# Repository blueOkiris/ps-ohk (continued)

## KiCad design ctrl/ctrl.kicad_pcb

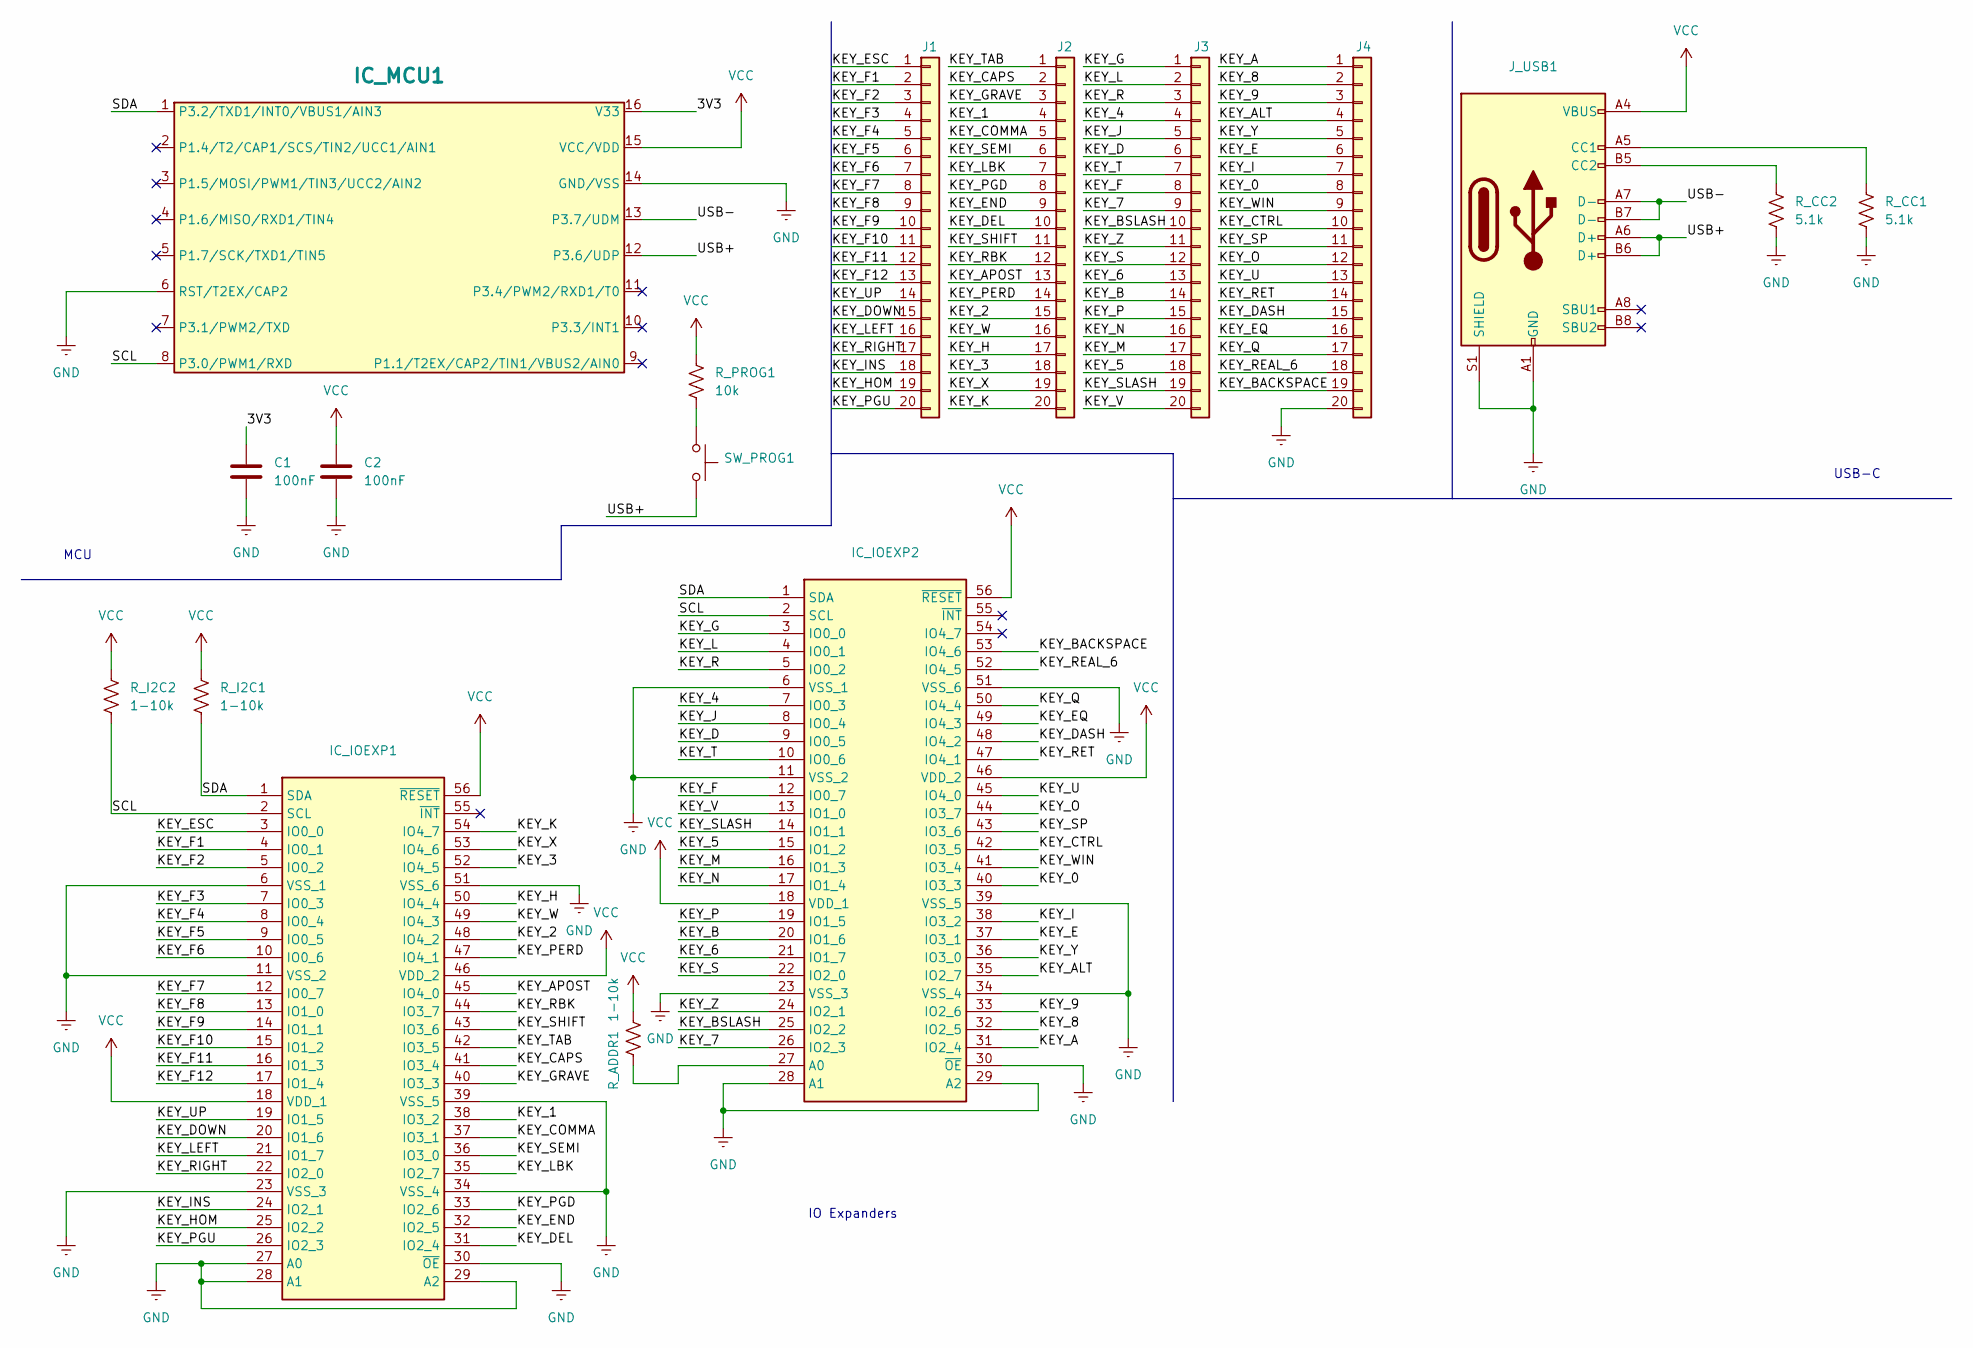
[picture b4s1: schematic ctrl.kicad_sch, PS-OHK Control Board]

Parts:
C1, C2: 100nF; C_0603_1608Metric
IC_IOEXP1, IC_IOEXP2: SOP50P810X120-56N; Mouser Part Number 771-PCA9505DGGY
IC_MCU1: SOIC-16_3.9x9.9mm_Pitch1.27mm
J1, J2, J3, J4: Conn_01x20; PinHeader_1x20_P2.54mm_Vertical
J_USB1: USB_C_Receptacle_HCTL_HC-TYPE-C-16P-01A
R_ADDR1: 1-10k; R_0603_1608Metric
R_CC1, R_CC2: 5.1k; R_0603_1608Metric
R_I2C1, R_I2C2: 1-10k; R_0603_1608Metric
R_PROG1: 10k; R_0603_1608Metric
SW_PROG1: SW_Push_1P1T_NO_6x6mm_H9.5mm

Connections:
/3V3: C1.1, IC_MCU1.16 (V33)
/KEY_0: IC_IOEXP2.40 (IO3_3), J4.8
/KEY_1: IC_IOEXP1.38 (IO3_2), J2.4
/KEY_2: IC_IOEXP1.48 (IO4_2), J2.15
/KEY_3: IC_IOEXP1.52 (IO4_5), J2.18
/KEY_4: IC_IOEXP2.7 (IO0_3), J3.4
/KEY_5: IC_IOEXP2.15 (IO1_2), J3.18
/KEY_6: IC_IOEXP2.21 (IO1_7), J3.13
/KEY_7: IC_IOEXP2.26 (IO2_3), J3.9
/KEY_8: IC_IOEXP2.32 (IO2_5), J4.2
/KEY_9: IC_IOEXP2.33 (IO2_6), J4.3
/KEY_A: IC_IOEXP2.31 (IO2_4), J4.1
/KEY_ALT: IC_IOEXP2.35 (IO2_7), J4.4
/KEY_APOST: IC_IOEXP1.45 (IO4_0), J2.13
/KEY_B: IC_IOEXP2.20 (IO1_6), J3.14
/KEY_BACKSPACE: IC_IOEXP2.53 (IO4_6), J4.19
/KEY_BSLASH: IC_IOEXP2.25 (IO2_2), J3.10
/KEY_CAPS: IC_IOEXP1.41 (IO3_4), J2.2
/KEY_COMMA: IC_IOEXP1.37 (IO3_1), J2.5
/KEY_CTRL: IC_IOEXP2.42 (IO3_5), J4.10
/KEY_D: IC_IOEXP2.9 (IO0_5), J3.6
/KEY_DASH: IC_IOEXP2.48 (IO4_2), J4.15
/KEY_DEL: IC_IOEXP1.31 (IO2_4), J2.10
/KEY_DOWN: IC_IOEXP1.20 (IO1_6), J1.15
/KEY_E: IC_IOEXP2.37 (IO3_1), J4.6
/KEY_END: IC_IOEXP1.32 (IO2_5), J2.9
/KEY_EQ: IC_IOEXP2.49 (IO4_3), J4.16
/KEY_ESC: IC_IOEXP1.3 (IO0_0), J1.1
/KEY_F: IC_IOEXP2.12 (IO0_7), J3.8
/KEY_F1: IC_IOEXP1.4 (IO0_1), J1.2
/KEY_F2: IC_IOEXP1.5 (IO0_2), J1.3
/KEY_F3: IC_IOEXP1.7 (IO0_3), J1.4
/KEY_F4: IC_IOEXP1.8 (IO0_4), J1.5
/KEY_F5: IC_IOEXP1.9 (IO0_5), J1.6
/KEY_F6: IC_IOEXP1.10 (IO0_6), J1.7
/KEY_F7: IC_IOEXP1.12 (IO0_7), J1.8
/KEY_F8: IC_IOEXP1.13 (IO1_0), J1.9
/KEY_F9: IC_IOEXP1.14 (IO1_1), J1.10
/KEY_F10: IC_IOEXP1.15 (IO1_2), J1.11
/KEY_F11: IC_IOEXP1.16 (IO1_3), J1.12
/KEY_F12: IC_IOEXP1.17 (IO1_4), J1.13
/KEY_G: IC_IOEXP2.3 (IO0_0), J3.1
/KEY_GRAVE: IC_IOEXP1.40 (IO3_3), J2.3
/KEY_H: IC_IOEXP1.50 (IO4_4), J2.17
/KEY_HOM: IC_IOEXP1.25 (IO2_2), J1.19
/KEY_I: IC_IOEXP2.38 (IO3_2), J4.7
/KEY_INS: IC_IOEXP1.24 (IO2_1), J1.18
/KEY_J: IC_IOEXP2.8 (IO0_4), J3.5
/KEY_K: IC_IOEXP1.54 (IO4_7), J2.20
/KEY_L: IC_IOEXP2.4 (IO0_1), J3.2
/KEY_LBK: IC_IOEXP1.35 (IO2_7), J2.7
/KEY_LEFT: IC_IOEXP1.21 (IO1_7), J1.16
/KEY_M: IC_IOEXP2.16 (IO1_3), J3.17
/KEY_N: IC_IOEXP2.17 (IO1_4), J3.16
/KEY_O: IC_IOEXP2.44 (IO3_7), J4.12
/KEY_P: IC_IOEXP2.19 (IO1_5), J3.15
/KEY_PERD: IC_IOEXP1.47 (IO4_1), J2.14
/KEY_PGD: IC_IOEXP1.33 (IO2_6), J2.8
/KEY_PGU: IC_IOEXP1.26 (IO2_3), J1.20
/KEY_Q: IC_IOEXP2.50 (IO4_4), J4.17
/KEY_R: IC_IOEXP2.5 (IO0_2), J3.3
/KEY_RBK: IC_IOEXP1.44 (IO3_7), J2.12
/KEY_REAL_6: IC_IOEXP2.52 (IO4_5), J4.18
/KEY_RET: IC_IOEXP2.47 (IO4_1), J4.14
/KEY_RIGHT: IC_IOEXP1.22 (IO2_0), J1.17
/KEY_S: IC_IOEXP2.22 (IO2_0), J3.12
/KEY_SEMI: IC_IOEXP1.36 (IO3_0), J2.6
/KEY_SHIFT: IC_IOEXP1.43 (IO3_6), J2.11
/KEY_SLASH: IC_IOEXP2.14 (IO1_1), J3.19
/KEY_SP: IC_IOEXP2.43 (IO3_6), J4.11
/KEY_T: IC_IOEXP2.10 (IO0_6), J3.7
/KEY_TAB: IC_IOEXP1.42 (IO3_5), J2.1
/KEY_U: IC_IOEXP2.45 (IO4_0), J4.13
/KEY_UP: IC_IOEXP1.19 (IO1_5), J1.14
/KEY_V: IC_IOEXP2.13 (IO1_0), J3.20
/KEY_W: IC_IOEXP1.49 (IO4_3), J2.16
/KEY_WIN: IC_IOEXP2.41 (IO3_4), J4.9
/KEY_X: IC_IOEXP1.53 (IO4_6), J2.19
/KEY_Y: IC_IOEXP2.36 (IO3_0), J4.5
/KEY_Z: IC_IOEXP2.24 (IO2_1), J3.11
/SCL: IC_IOEXP1.2 (SCL), IC_IOEXP2.2 (SCL), IC_MCU1.8 (P3.0/PWM1/RXD), R_I2C2.2
/SDA: IC_IOEXP1.1 (SDA), IC_IOEXP2.1 (SDA), IC_MCU1.1 (P3.2/TXD1/INT0/VBUS1/AIN3), R_I2C1.2
/USB+: IC_MCU1.12 (P3.6/UDP), J_USB1.A6 (D+), J_USB1.B6 (D+), SW_PROG1.2
/USB-: IC_MCU1.13 (P3.7/UDM), J_USB1.A7 (D-), J_USB1.B7 (D-)
GND: C1.2, C2.2, IC_IOEXP1.6 (VSS_1), IC_IOEXP1.11 (VSS_2), IC_IOEXP1.23 (VSS_3), IC_IOEXP1.27 (A0), IC_IOEXP1.28 (A1), IC_IOEXP1.29 (A2), IC_IOEXP1.30 (~OE), IC_IOEXP1.34 (VSS_4), IC_IOEXP1.39 (VSS_5), IC_IOEXP1.51 (VSS_6), IC_IOEXP2.6 (VSS_1), IC_IOEXP2.11 (VSS_2), IC_IOEXP2.23 (VSS_3), IC_IOEXP2.28 (A1), IC_IOEXP2.29 (A2), IC_IOEXP2.30 (~OE), IC_IOEXP2.34 (VSS_4), IC_IOEXP2.39 (VSS_5), IC_IOEXP2.51 (VSS_6), IC_MCU1.6 (RST/T2EX/CAP2), IC_MCU1.14 (GND/VSS), J4.20, J_USB1.A1 (GND), J_USB1.A12 (GND), J_USB1.B1 (GND), J_USB1.B12 (GND), J_USB1.S1 (SHIELD), R_CC1.2, R_CC2.2
unnamed: IC_IOEXP2.27 (A0), R_ADDR1.2
unnamed: J_USB1.A5 (CC1), R_CC1.1
unnamed: J_USB1.B5 (CC2), R_CC2.1
unnamed: R_PROG1.2, SW_PROG1.1
VCC: C2.1, IC_IOEXP1.18 (VDD_1), IC_IOEXP1.46 (VDD_2), IC_IOEXP1.56 (~RESET), IC_IOEXP2.18 (VDD_1), IC_IOEXP2.46 (VDD_2), IC_IOEXP2.56 (~RESET), IC_MCU1.15 (VCC/VDD), J_USB1.A4 (VBUS), J_USB1.A9 (VBUS), J_USB1.B4 (VBUS), J_USB1.B9 (VBUS), R_ADDR1.1, R_I2C1.1, R_I2C2.1, R_PROG1.1

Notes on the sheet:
IO Expanders
USB-C
MCU

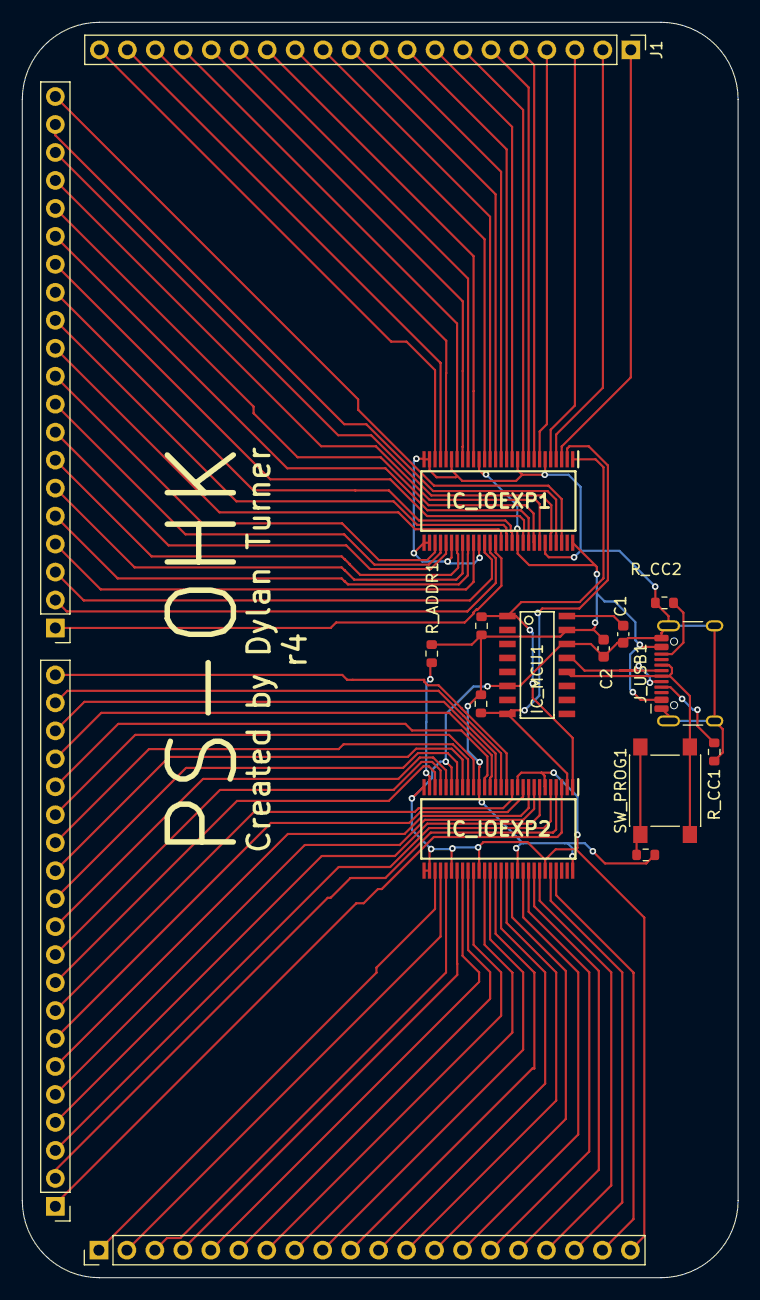
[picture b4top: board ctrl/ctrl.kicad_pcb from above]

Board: 2 copper layers, 65.0 x 114.0 mm, 17 parts (0 on the bottom side), 90 nets.

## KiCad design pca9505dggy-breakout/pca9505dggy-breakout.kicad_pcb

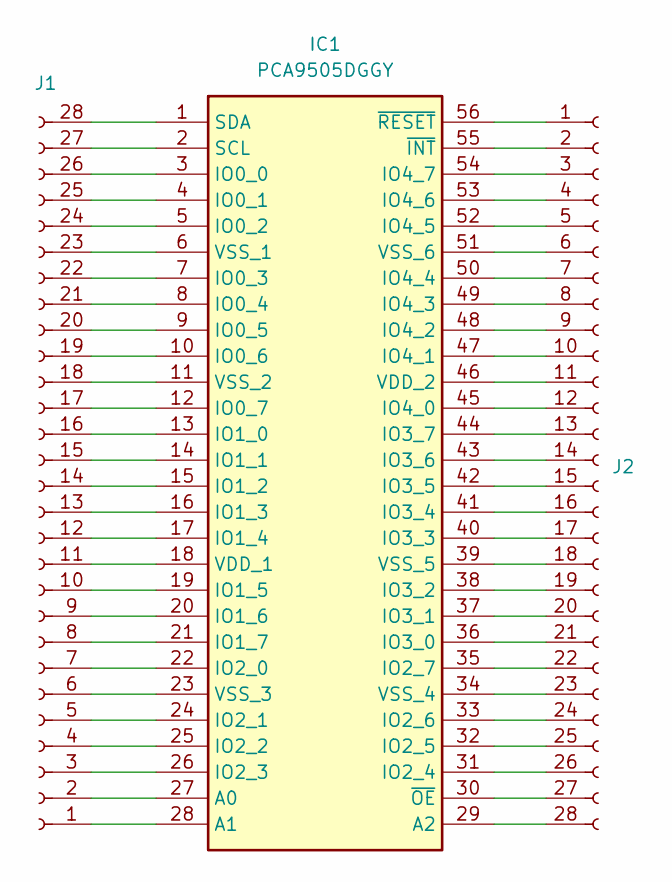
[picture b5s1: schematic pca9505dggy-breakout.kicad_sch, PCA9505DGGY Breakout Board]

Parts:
IC1: PCA9505DGGY; SOP50P810X120-56N; Mouser Part Number 771-PCA9505DGGY
J1, J2: PinHeader_1x28_P2.54mm_Vertical

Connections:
unnamed: IC1.27 (A0), J1.2
unnamed: IC1.28 (A1), J1.1
unnamed: IC1.29 (A2), J2.28
unnamed: IC1.3 (IO0_0), J1.26
unnamed: IC1.4 (IO0_1), J1.25
unnamed: IC1.5 (IO0_2), J1.24
unnamed: IC1.7 (IO0_3), J1.22
unnamed: IC1.8 (IO0_4), J1.21
unnamed: IC1.9 (IO0_5), J1.20
unnamed: IC1.10 (IO0_6), J1.19
unnamed: IC1.12 (IO0_7), J1.17
unnamed: IC1.13 (IO1_0), J1.16
unnamed: IC1.14 (IO1_1), J1.15
unnamed: IC1.15 (IO1_2), J1.14
unnamed: IC1.16 (IO1_3), J1.13
unnamed: IC1.17 (IO1_4), J1.12
unnamed: IC1.19 (IO1_5), J1.10
unnamed: IC1.20 (IO1_6), J1.9
unnamed: IC1.21 (IO1_7), J1.8
unnamed: IC1.22 (IO2_0), J1.7
unnamed: IC1.24 (IO2_1), J1.5
unnamed: IC1.25 (IO2_2), J1.4
unnamed: IC1.26 (IO2_3), J1.3
unnamed: IC1.31 (IO2_4), J2.26
unnamed: IC1.32 (IO2_5), J2.25
unnamed: IC1.33 (IO2_6), J2.24
unnamed: IC1.35 (IO2_7), J2.22
unnamed: IC1.36 (IO3_0), J2.21
unnamed: IC1.37 (IO3_1), J2.20
unnamed: IC1.38 (IO3_2), J2.19
unnamed: IC1.40 (IO3_3), J2.17
unnamed: IC1.41 (IO3_4), J2.16
unnamed: IC1.42 (IO3_5), J2.15
unnamed: IC1.43 (IO3_6), J2.14
unnamed: IC1.44 (IO3_7), J2.13
unnamed: IC1.45 (IO4_0), J2.12
unnamed: IC1.47 (IO4_1), J2.10
unnamed: IC1.48 (IO4_2), J2.9
unnamed: IC1.49 (IO4_3), J2.8
unnamed: IC1.50 (IO4_4), J2.7
unnamed: IC1.52 (IO4_5), J2.5
unnamed: IC1.53 (IO4_6), J2.4
unnamed: IC1.54 (IO4_7), J2.3
unnamed: IC1.2 (SCL), J1.27
unnamed: IC1.1 (SDA), J1.28
unnamed: IC1.18 (VDD_1), J1.11
unnamed: IC1.46 (VDD_2), J2.11
unnamed: IC1.6 (VSS_1), J1.23
unnamed: IC1.11 (VSS_2), J1.18
unnamed: IC1.23 (VSS_3), J1.6
unnamed: IC1.34 (VSS_4), J2.23
unnamed: IC1.39 (VSS_5), J2.18
unnamed: IC1.51 (VSS_6), J2.6
unnamed: IC1.55 (~INT), J2.2
unnamed: IC1.30 (~OE), J2.27
unnamed: IC1.56 (~RESET), J2.1

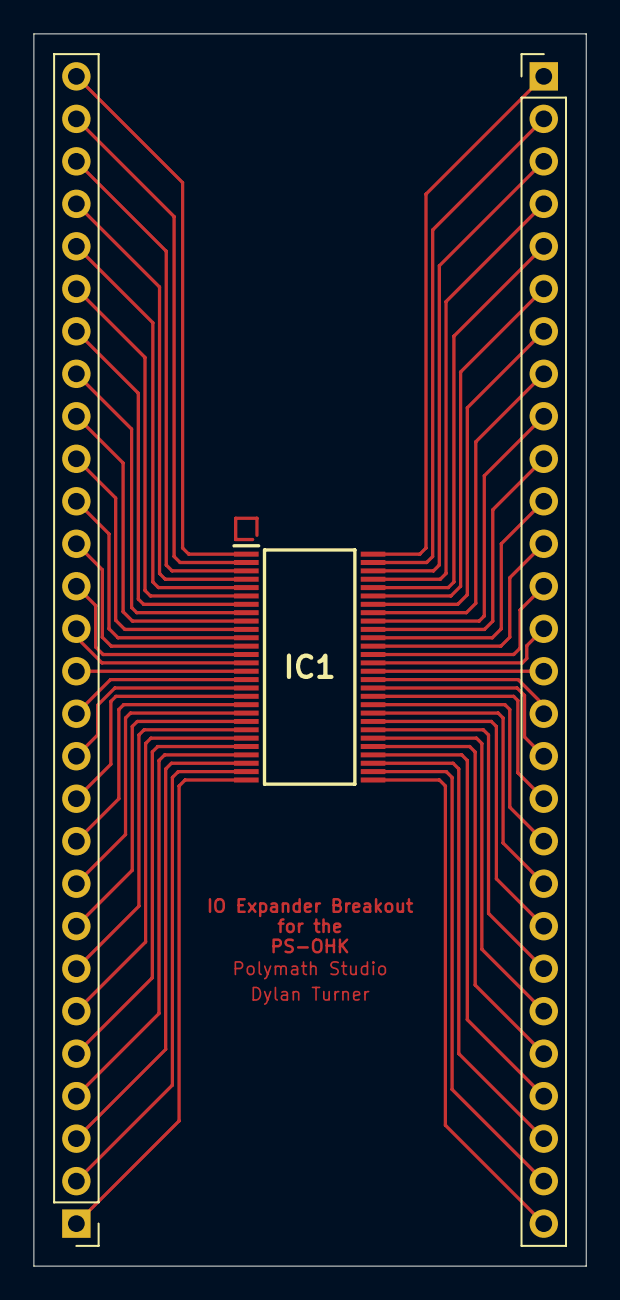
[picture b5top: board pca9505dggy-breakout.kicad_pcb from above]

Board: 2 copper layers, 33.0 x 73.7 mm, 3 parts (0 on the bottom side), 56 nets.

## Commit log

2024-05-06 Initial commit: pcb w/ switches and layout derived
2024-05-06 LICENSE: GPL
2024-05-06 Added 40-pin IO Expander to project
    Will make use of two of them
2024-05-09 pca9505ddgy-breakout: dev board for GPIO expander
2024-05-09 firmware: created folder for keyboard code
    And compile tools submodule
2024-05-16 fw: got HID working via CH55xDuino
2024-05-16 fw: working pca9505 driver
2024-05-16 pcb: implement IO Expander circuit based on proto
2024-05-16 pcb: moved libraries into pcb folder for org.
2024-05-16 pca9505dggy-breakout-pcb: correct lib paths
2024-05-21 pcb: add buttons and route
2024-05-25 gitignore: removed *.gbr
2024-06-01 pcb: made orderable on pcb-way
2024-06-01 fw: implement full keyboard func (untested)
2024-06-15 pcb: added C and rmd unneeded hardware
2024-06-15 fw: added c and made last keys work
2024-06-15 shell: add prog for checking keys
2024-06-15 README: add pic
2024-06-15 README: add build instructions
2024-06-15 fw: alt + backspace = delete
2024-06-16 keyboard: fixed delete key
2024-06-18 pcb: add backspace and move k
2024-06-18 fw: ad true delete since now bs key
2024-06-24 pcb: split into a control board and a keys board
    Reasoning:
    1. Should be cheaper to order an assembled control board + unassembled
    main board
    2. More flexible (can create a right-handed board as well)
2024-06-24 Duplicated left-hand to make a right-handed vers
2024-06-25 keys-righthand: wired up
2024-06-25 Ctrl+Keys: Fixed BOM/rmvd unused
2024-06-25 pcb: Update revision numbers
2024-06-27 pic: show r2
2024-07-01 enclosure: initial version of right handed case
2024-07-01 Rm accidentally added outputs
2024-07-09 enclosure: modify to correct fit and add slot
2024-09-10 r4: 1mm->2.54mm pins, no right-hand yet
2024-09-10 enlosure: enclosure for right-handed
2025-06-06 Saving whatever I had done
2025-06-07 pcbs: reworked ctrl, io, and left-hand
    - Still need to do right-hand
    - Will need to do a new key map as well
